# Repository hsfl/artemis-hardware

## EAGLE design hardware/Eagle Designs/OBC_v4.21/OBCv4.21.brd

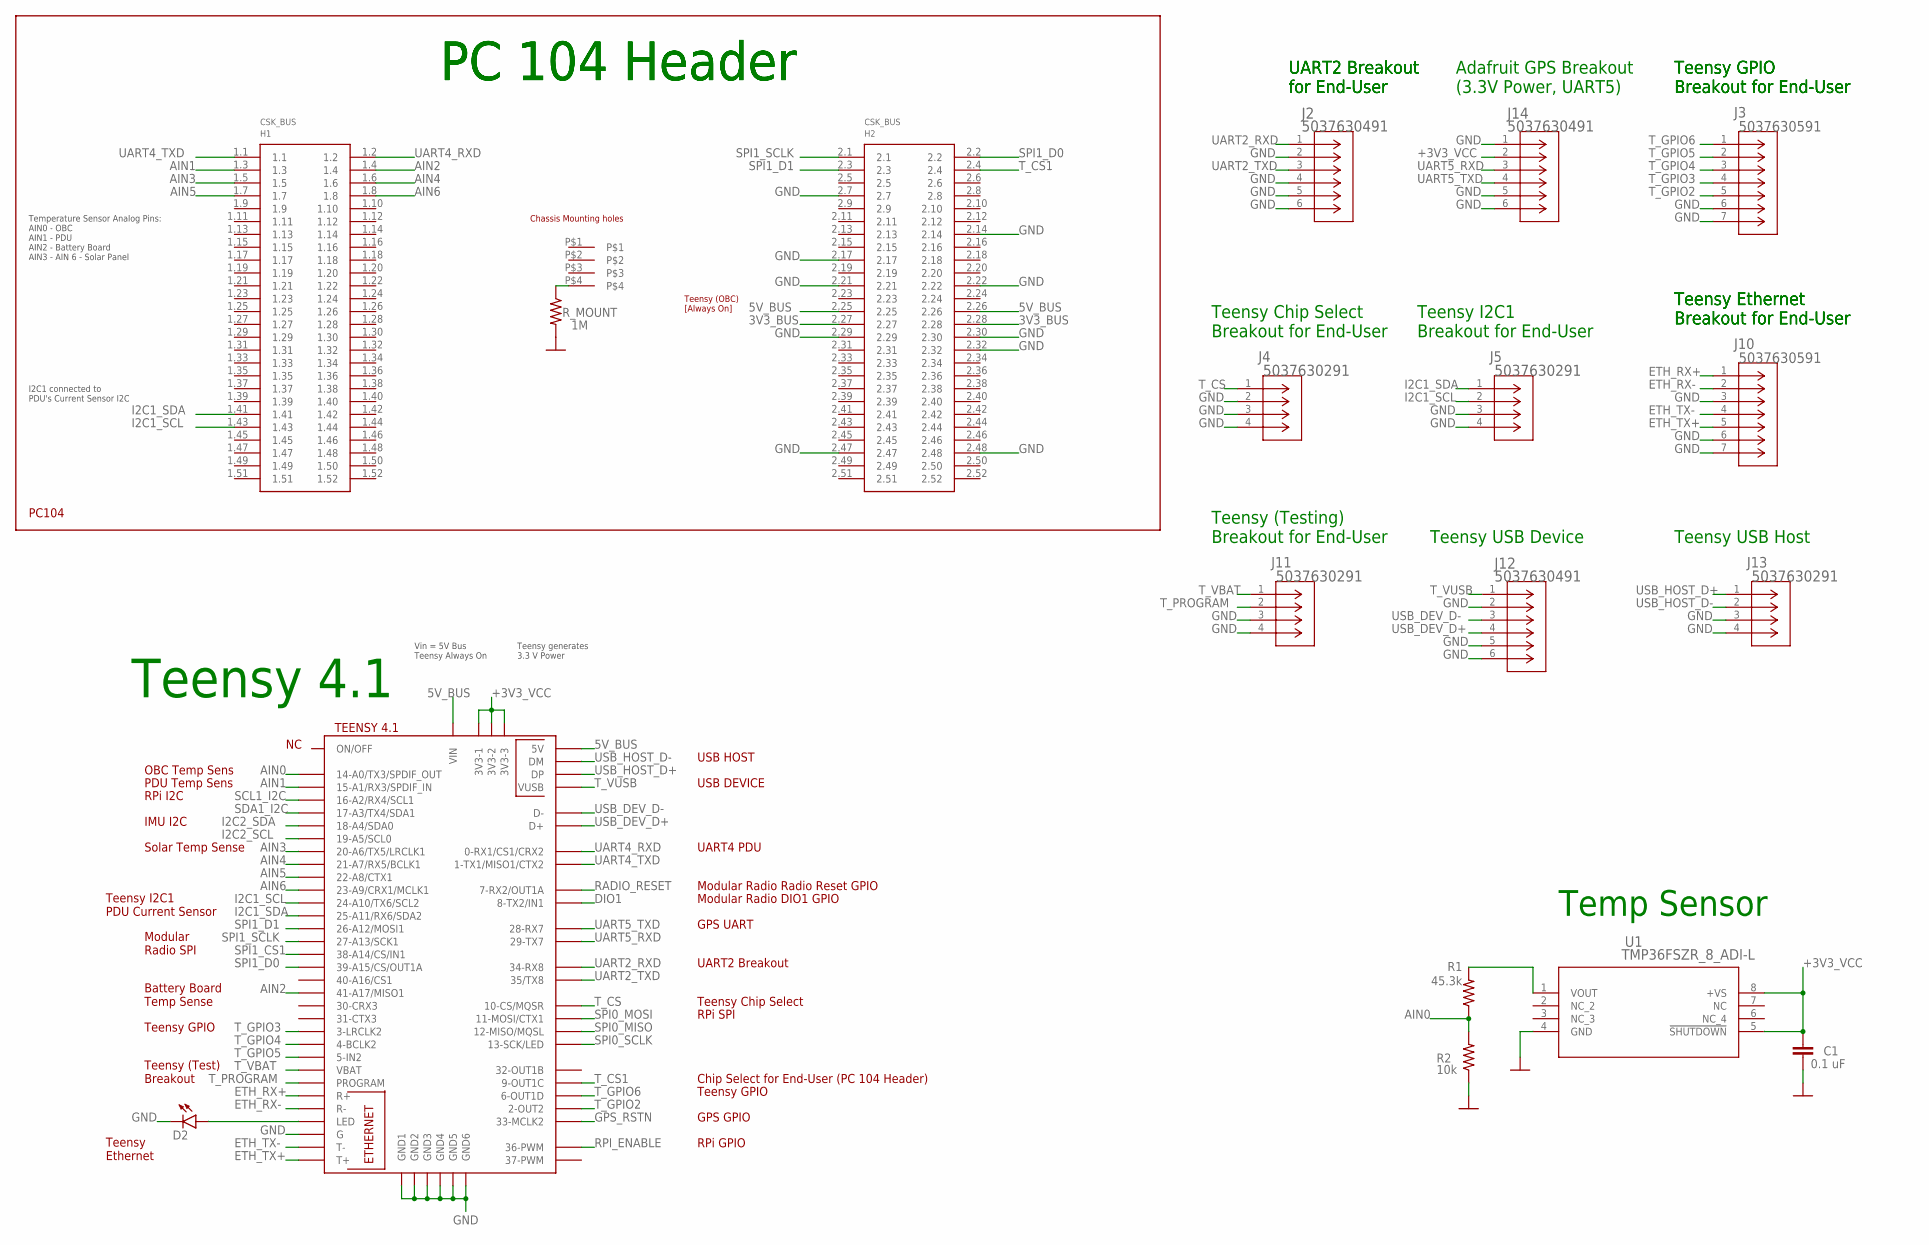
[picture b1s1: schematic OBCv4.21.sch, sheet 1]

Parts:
C1: 0.1 uF; 0805
D2: LEDCHIP-LED0603; CHIP-LED0603
H1: PC104_WCONN
J2, J12, J14: 5037630491; CON_5037630491
J3, J10: 5037630591; CON_5037630591
J4, J5, J11, J13: 5037630291; CON_5037630291
R1: 45.3k; 0805
R2: 10k; 0805
R_MOUNT: 1M; 0805
U1: TMP36FSZR_8_ADI-L; R_8_ADI-L
U$1: TEENSY41

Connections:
3V3_BUS: H1.2.27, H1.2.28; also elsewhere on the board
5V_BUS: H1.2.25, H1.2.26, U$1.+5V (5V), U$1.VIN; also elsewhere on the board
+3V3_VCC: C1.1, J14.2, U1.5 (!SHUTDOWN), U1.8 (+VS), U$1.3V3-1, U$1.3V3-2, U$1.3V3-3; also elsewhere on the board
AIN0: R1.1, R2.2, U$1.14-A0/TX3/SPDIF_OUT
AIN1: H1.1.3, U$1.15-A1/RX3/SPDIF_IN
AIN2: H1.1.4, U$1.41-A17/MISO1
AIN3: H1.1.5, U$1.20-A6/TX5/LRCLK1
AIN4: H1.1.6, U$1.21-A7/RX5/BCLK1
AIN5: H1.1.7, U$1.22-A8/CTX1
AIN6: H1.1.8, U$1.23-A9/CRX1/MCLK1
DIO1: U$1.8-TX2/IN1; also elsewhere on the board
ETH_RX+: J10.1, U$1.R+
ETH_RX-: J10.2, U$1.R-
ETH_TX+: J10.5, U$1.T+
ETH_TX-: J10.4, U$1.T-
GND: C1.2, D2.C, H1.2.7, H1.2.14, H1.2.17, H1.2.21, H1.2.22, H1.2.29, H1.2.30, H1.2.32, H1.2.47, H1.2.48, J2.2, J2.4, J2.5, J2.6, J3.6, J3.7, J4.2, J4.3, J4.4, J5.3, J5.4, J10.3, J10.6, J10.7, J11.3, J11.4, J12.2, J12.5, J12.6, J13.3, J13.4, J14.1, J14.5, J14.6, R2.1, R_MOUNT.2, U1.4 (GND), U$1.G, U$1.GND1, U$1.GND2, U$1.GND3, U$1.GND4, U$1.GND5, U$1.GND6; also elsewhere on the board
GPS_RSTN: U$1.33-MCLK2; also elsewhere on the board
I2C1_SCL: H1.1.43, J5.2, U$1.24-A10/TX6/SCL2
I2C1_SDA: H1.1.41, J5.1, U$1.25-A11/RX6/SDA2
I2C2_SCL: U$1.19-A5/SCL0; also elsewhere on the board
I2C2_SDA: U$1.18-A4/SDA0; also elsewhere on the board
unnamed: D2.A, U$1.LED
unnamed: R1.2, U1.1 (VOUT)
unnamed: H1.P$4, R_MOUNT.1
RADIO_RESET: U$1.7-RX2/OUT1A; also elsewhere on the board
RPI_ENABLE: U$1.36-PWM; also elsewhere on the board
SCL1_I2C: U$1.16-A2/RX4/SCL1; also elsewhere on the board
SDA1_I2C: U$1.17-A3/TX4/SDA1; also elsewhere on the board
SPI0_MISO: U$1.12-MISO/MQSL; also elsewhere on the board
SPI0_MOSI: U$1.11-MOSI/CTX1; also elsewhere on the board
SPI0_SCLK: U$1.13-SCK/LED; also elsewhere on the board
SPI1_CS1: U$1.38-A14/CS/IN1; also elsewhere on the board
SPI1_D0: H1.2.2, U$1.39-A15/CS/OUT1A; also elsewhere on the board
SPI1_D1: H1.2.3, U$1.26-A12/MOSI1; also elsewhere on the board
SPI1_SCLK: H1.2.1, U$1.27-A13/SCK1; also elsewhere on the board
T_CS: J4.1, U$1.10-CS\MQSR (10-CS/MQSR)
T_CS1: H1.2.4, U$1.9-OUT1C
T_GPIO2: J3.5, U$1.2-OUT2
T_GPIO3: J3.4, U$1.3-LRCLK2
T_GPIO4: J3.3, U$1.4-BCLK2
T_GPIO5: J3.2, U$1.5-IN2
T_GPIO6: J3.1, U$1.6-OUT1D
T_PROGRAM: J11.2, U$1.PROGRAM
T_VBAT: J11.1, U$1.VBAT
T_VUSB: J12.1, U$1.VUSB
UART2_RXD: J2.1, U$1.34-RX8
UART2_TXD: J2.3, U$1.35-TX8 (35/TX8)
UART4_RXD: H1.1.2, U$1.0-RX1/CS1/CRX2
UART4_TXD: H1.1.1, U$1.1-TX1/MISO1/CTX2
UART5_RXD: J14.3, U$1.29-TX7; also elsewhere on the board
UART5_TXD: J14.4, U$1.28-RX7; also elsewhere on the board
USB_DEV_D+: J12.4, U$1.D+
USB_DEV_D-: J12.3, U$1.D-
USB_HOST_D+: J13.1, U$1.DP
USB_HOST_D-: J13.2, U$1.DM

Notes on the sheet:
Temp Sensor
PC 104 Header
Temperature Sensor Analog Pins: AIN0 - OBC AIN1 - PDU AIN2 - Battery Board AIN3 - AIN 6 - Solar Panel
UART2 Breakout for End-User
Teensy 4.1
Teensy GPIO Breakout for End-User
Teensy Chip Select Breakout for End-User
Teensy I2C1 Breakout for End-User
OBC Temp Sens
PDU Temp Sens
RPi I2C
IMU I2C
Solar Temp Sense
Teensy I2C1 PDU Current Sensor
Modular Radio SPI
Battery Board Temp Sense
Teensy GPIO
Teensy (Test) Breakout
Teensy Ethernet
RPi GPIO
GPS GPIO
RPi SPI
Teensy Chip Select
UART2 Breakout
GPS UART
Modular Radio Radio Reset GPIO
UART4 PDU
USB HOST
USB DEVICE
Teensy Ethernet Breakout for End-User
Teensy (Testing) Breakout for End-User
Teensy USB Device
Teensy USB Host
Teensy (OBC) [Always On]
Vin = 5V Bus Teensy Always On
Teensy generates 3.3 V Power
Adafruit GPS Breakout (3.3V Power, UART5)
Modular Radio DIO1 GPIO
I2C1 connected to PDU's Current Sensor I2C
Chip Select for End-User (PC 104 Header)

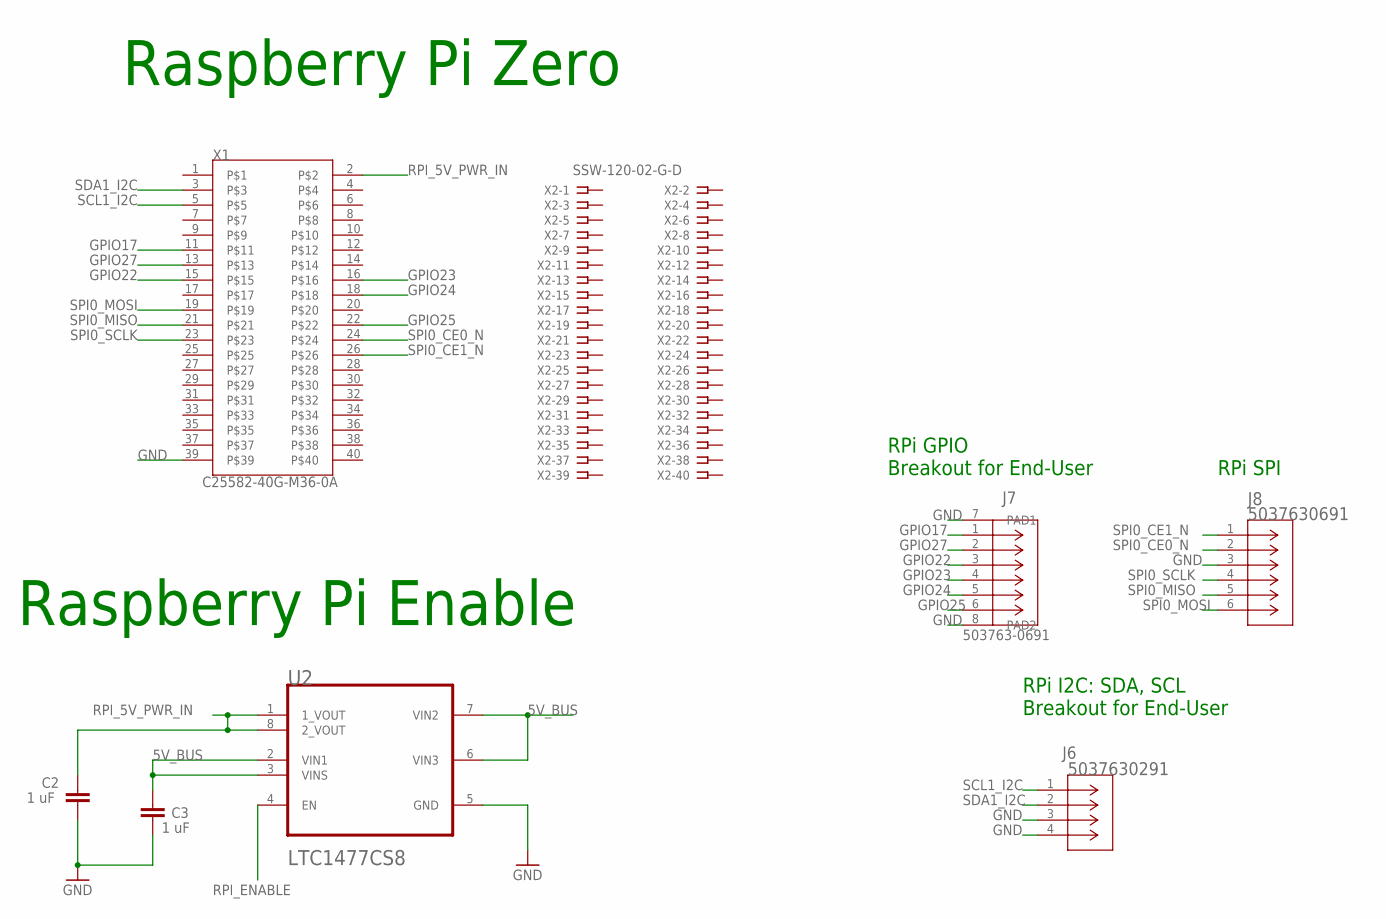
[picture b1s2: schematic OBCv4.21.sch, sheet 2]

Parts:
C2, C3: 1 uF; 0805
J6: 5037630291; CON_5037630291
J7: 503763-0691; CONN_503763-0691_MOL
J8: 5037630691; CONN_503763-0691_MOL
U2: LTC1477CS8LINEAR_TECHNOLOGY_LTC1477CS8_0_2; LINEAR_TECHNOLOGY_LTC1477CS8_2
X1: C25582-40G-M36-0A; ADAFRUIT_C25582-40G-M36-0A_0
X2: SSW-120-02-G-D

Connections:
5V_BUS: C3.1, U2.2 (VIN1), U2.3 (VINS), U2.6 (VIN3), U2.7 (VIN2); also elsewhere on the board
GND: C2.2, C3.2, J6.3, J6.4, J7.7 (PAD1), J7.8 (PAD2), J8.3, U2.5 (GND), X1.39; also elsewhere on the board
GPIO17: J7.1, X1.11
GPIO22: J7.3, X1.15
GPIO23: J7.4, X1.16
GPIO24: J7.5, X1.18
GPIO25: J7.6, X1.22
GPIO27: J7.2, X1.13
RPI_5V_PWR_IN: C2.1, U2.1 (1_VOUT), U2.8 (2_VOUT), X1.2
RPI_ENABLE: U2.4 (EN); also elsewhere on the board
SCL1_I2C: J6.1, X1.5; also elsewhere on the board
SDA1_I2C: J6.2, X1.3; also elsewhere on the board
SPI0_CE0_N: J8.2, X1.24
SPI0_CE1_N: J8.1, X1.26
SPI0_MISO: J8.5, X1.21; also elsewhere on the board
SPI0_MOSI: J8.6, X1.19; also elsewhere on the board
SPI0_SCLK: J8.4, X1.23; also elsewhere on the board

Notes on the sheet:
Raspberry Pi Zero
Raspberry Pi Enable
RPi I2C: SDA, SCL Breakout for End-User
RPi GPIO Breakout for End-User
RPi SPI

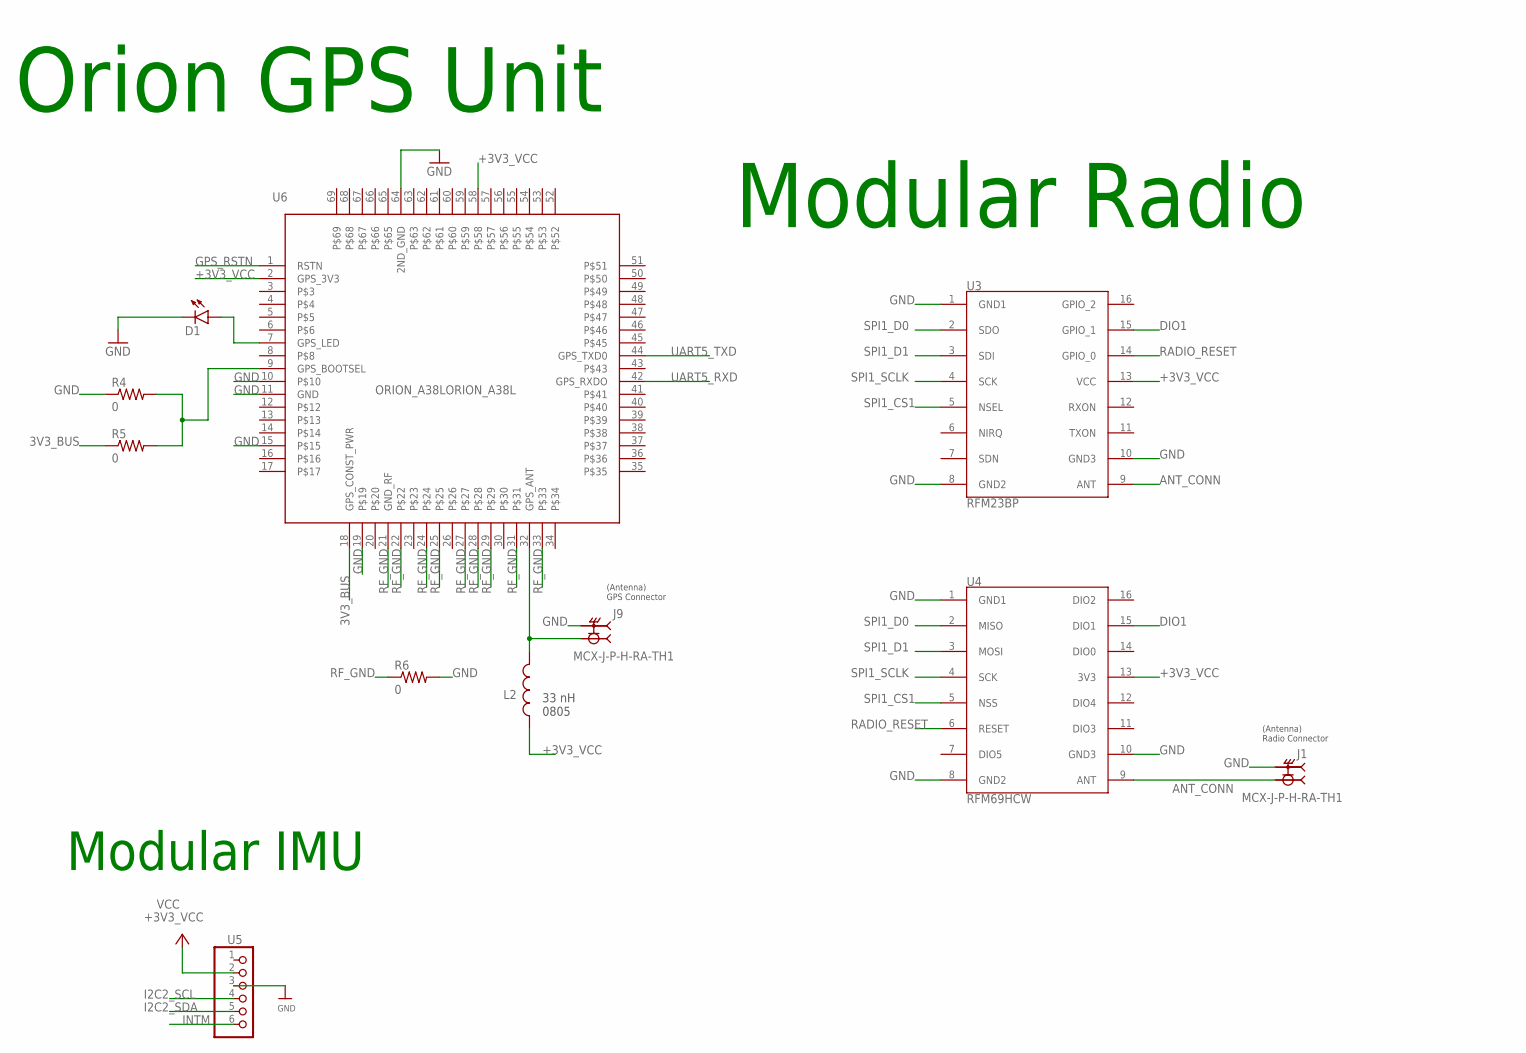
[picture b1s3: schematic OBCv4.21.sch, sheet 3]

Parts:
D1: LEDCHIP-LED0603; CHIP-LED0603
J1, J9: MCX-J-P-H-RA-TH1; SAMTEC_MCX-J-P-H-RA-TH1
L2: AIMC-0805-2N2S-T; INDC2012X105N
R4, R5, R6: 0; 0805
U3: RFM23BP
U4: RFM69HCW
U5: HEADER-1X670MIL; 1X06_ROUND_70
U6: ORION_A38LORION_A38L; ORION_A38L

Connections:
3V3_BUS: R5.1, U6.18 (GPS_CONST_PWR); also elsewhere on the board
+3V3_VCC: L2.1, U3.13 (VCC), U4.13 (3V3), U5.2, U6.2 (GPS_3V3), U6.58; also elsewhere on the board
ANT_CONN: J1.1, U3.9 (ANT), U4.9 (ANT)
DIO1: U3.15 (GPIO_1), U4.15 (DIO1); also elsewhere on the board
GND: D1.C, J1.S1 (2), J1.S2 (2), J1.S3 (2), J1.S4 (2), J9.S1 (2), J9.S2 (2), J9.S3 (2), J9.S4 (2), R4.1, R6.2, U3.1 (GND1), U3.8 (GND2), U3.10 (GND3), U4.1 (GND1), U4.8 (GND2), U4.10 (GND3), U5.3, U6.10, U6.11 (GND), U6.15, U6.19, U6.64 (2ND_GND); also elsewhere on the board
GPS_RSTN: U6.1 (RSTN); also elsewhere on the board
I2C2_SCL: U5.4; also elsewhere on the board
I2C2_SDA: U5.5; also elsewhere on the board
INTM: U5.6
unnamed: R4.2, R5.2, U6.9 (GPS_BOOTSEL)
unnamed: J9.1, L2.2, U6.32 (GPS_ANT)
unnamed: D1.A, U6.7 (GPS_LED)
RADIO_RESET: U3.14 (GPIO_0), U4.6 (RESET); also elsewhere on the board
RF_GND: R6.1, U6.21 (GND_RF), U6.22, U6.24, U6.25, U6.27, U6.28, U6.29, U6.31, U6.33
SPI1_CS1: U3.5 (NSEL), U4.5 (NSS); also elsewhere on the board
SPI1_D0: U3.2 (SDO), U4.2 (MISO); also elsewhere on the board
SPI1_D1: U3.3 (SDI), U4.3 (MOSI); also elsewhere on the board
SPI1_SCLK: U3.4 (SCK), U4.4 (SCK); also elsewhere on the board
UART5_RXD: U6.42 (GPS_RXDO); also elsewhere on the board
UART5_TXD: U6.44 (GPS_TXD0); also elsewhere on the board

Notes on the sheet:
Orion GPS Unit
Modular Radio
Modular IMU
(Antenna) Radio Connector
(Antenna) GPS Connector
33 nH 0805

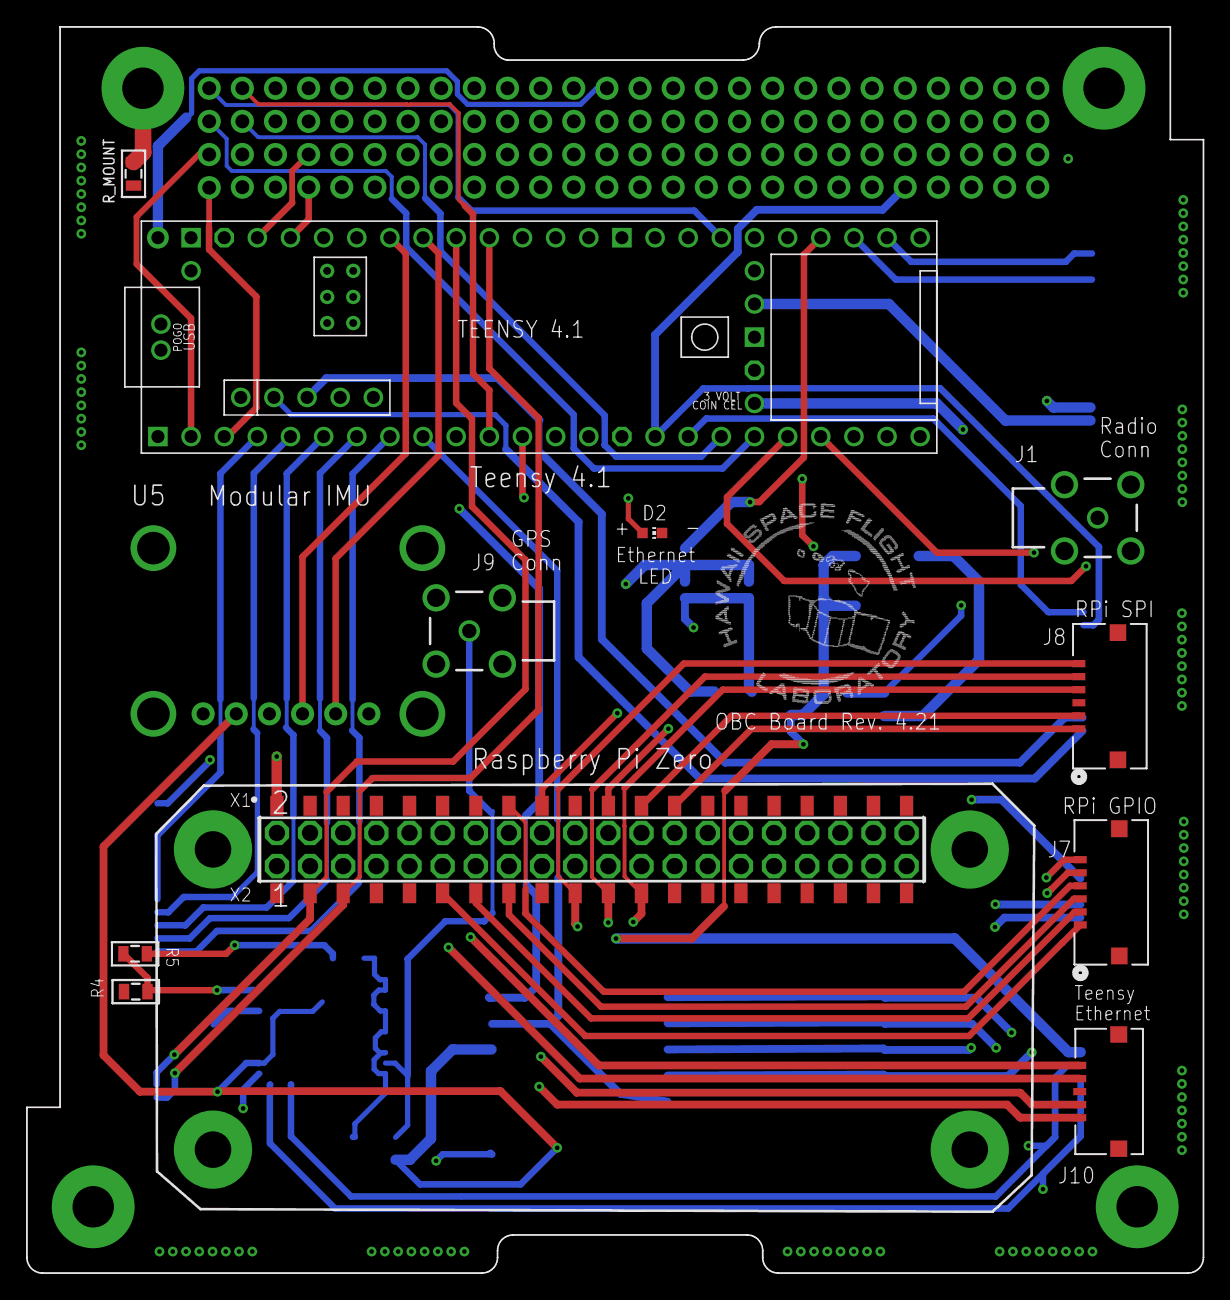
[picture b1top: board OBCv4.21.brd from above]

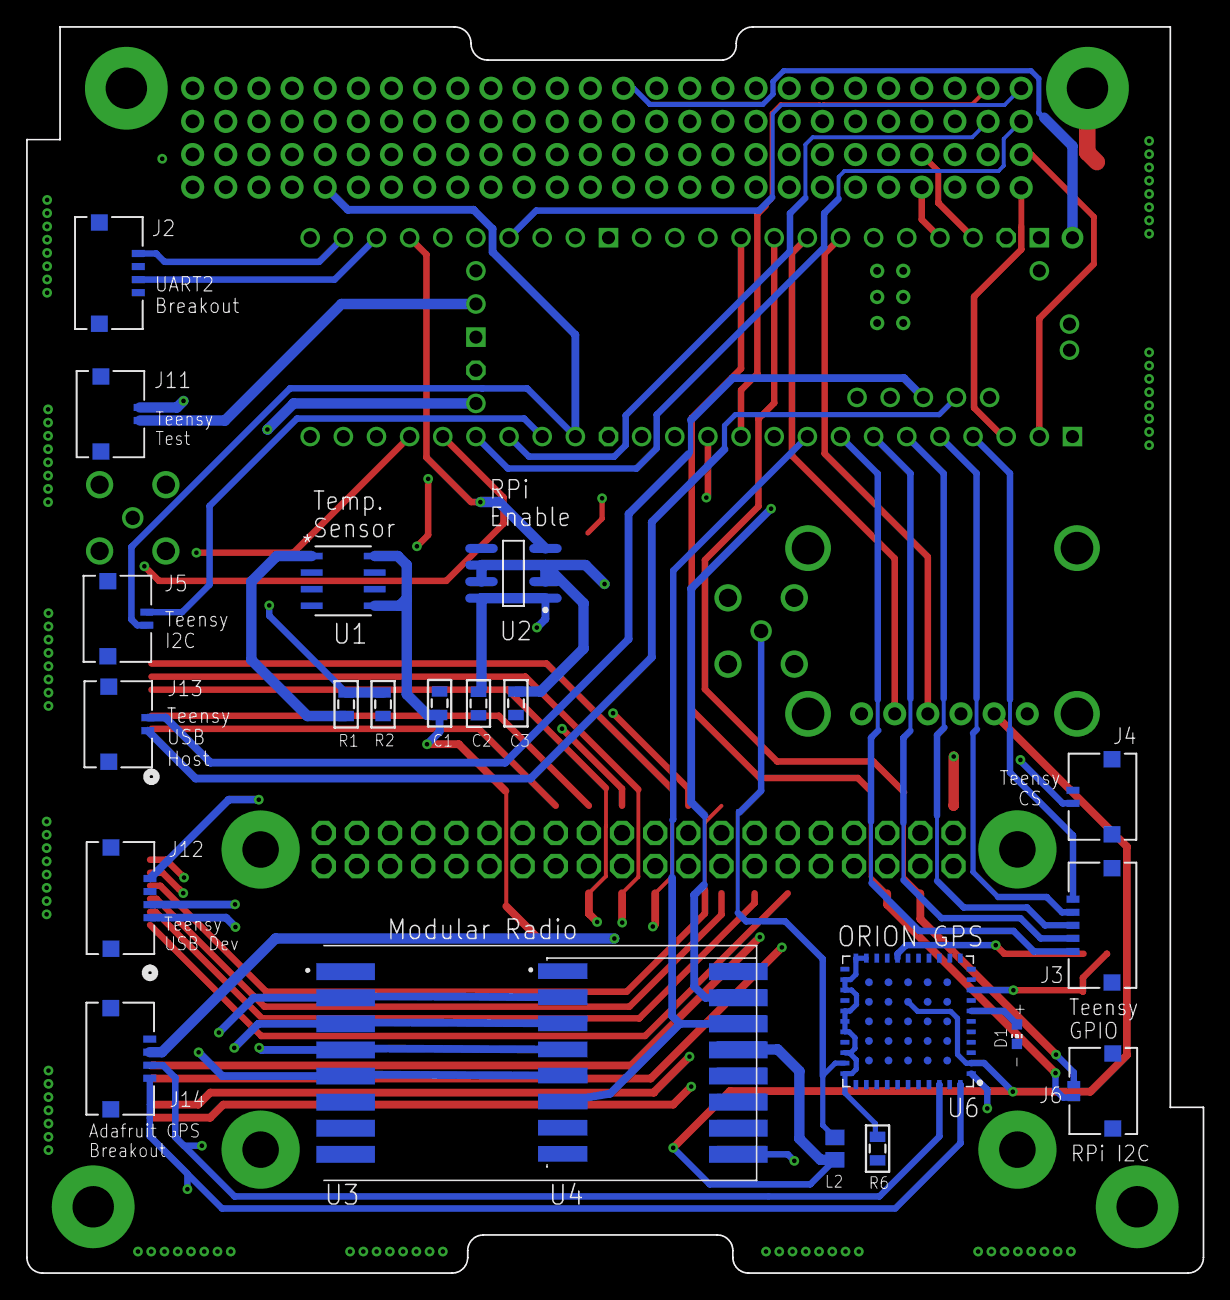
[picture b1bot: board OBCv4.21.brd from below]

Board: 4 copper layers, 90.2 x 95.5 mm, 36 parts (22 on the bottom side), 69 nets.

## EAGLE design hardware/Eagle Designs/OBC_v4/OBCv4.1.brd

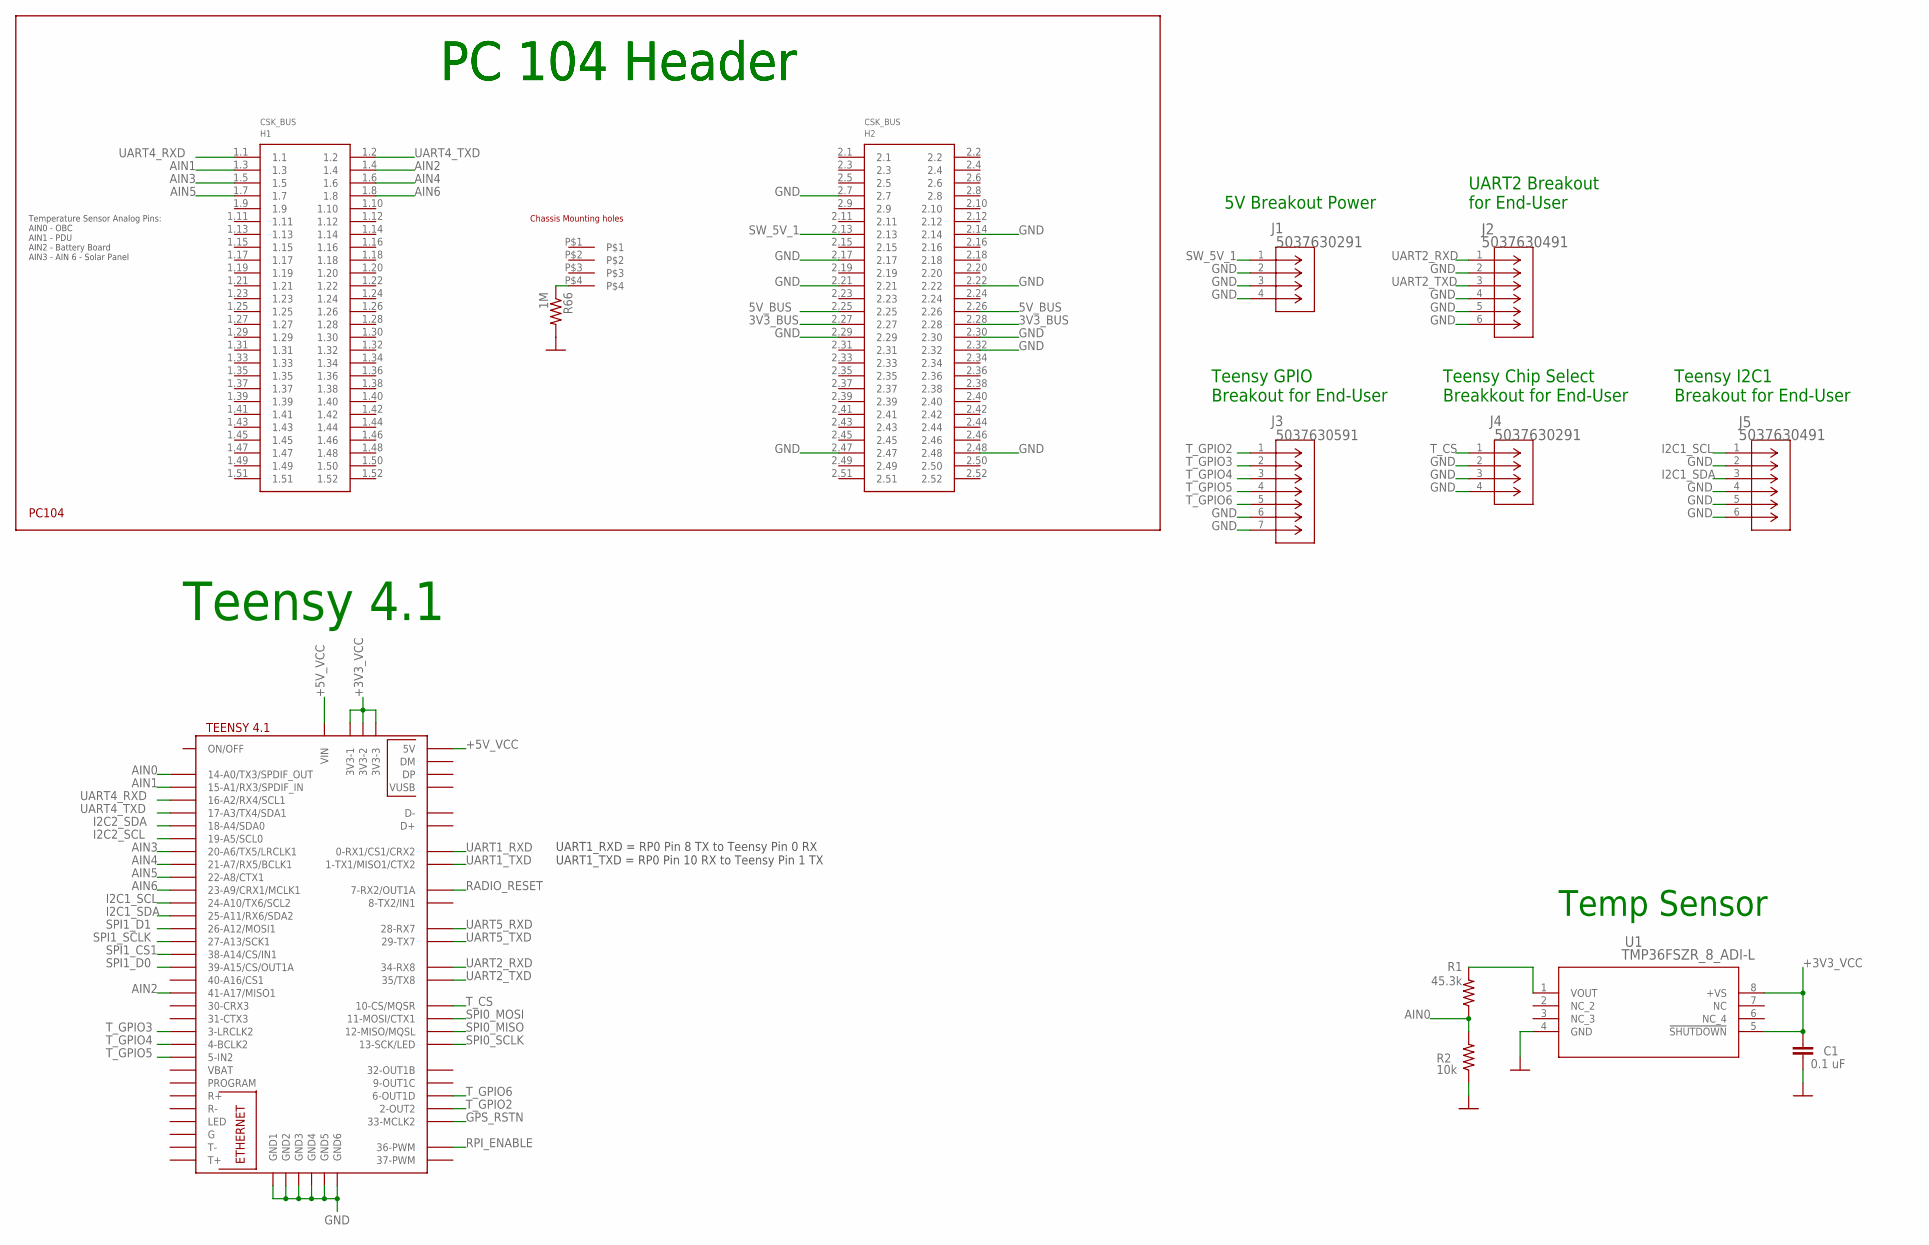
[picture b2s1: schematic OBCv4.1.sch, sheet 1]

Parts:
C1: 0.1 uF; 0805
H1: PC104_WCONN
J1, J4: 5037630291; CON_5037630291
J2, J5: 5037630491; CON_5037630491
J3: 5037630591; CON_5037630591
R1: 45.3k; 0805
R2: 10k; 0805
R66: 1M; 0805
U1: TMP36FSZR_8_ADI-L; R_8_ADI-L
U$1: TEENSY41

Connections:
3V3_BUS: H1.2.27, H1.2.28; also elsewhere on the board
5V_BUS: H1.2.25, H1.2.26
+3V3_VCC: C1.1, U1.5 (!SHUTDOWN), U1.8 (+VS), U$1.3V3-1, U$1.3V3-3; also elsewhere on the board
+5V_VCC: U$1.+5V (5V), U$1.VIN; also elsewhere on the board
AIN0: R1.1, R2.2, U$1.14-A0/TX3/SPDIF_OUT
AIN1: H1.1.3, U$1.15-A1/RX3/SPDIF_IN
AIN2: H1.1.4, U$1.41-A17/MISO1
AIN3: H1.1.5, U$1.20-A6/TX5/LRCLK1
AIN4: H1.1.6, U$1.21-A7/RX5/BCLK1
AIN5: H1.1.7, U$1.22-A8/CTX1
AIN6: H1.1.8, U$1.23-A9/CRX1/MCLK1
GND: C1.2, H1.2.7, H1.2.14, H1.2.17, H1.2.21, H1.2.22, H1.2.29, H1.2.30, H1.2.32, H1.2.47, H1.2.48, J1.2, J1.3, J1.4, J2.2, J2.4, J2.5, J2.6, J3.6, J3.7, J4.2, J4.3, J4.4, J5.2, J5.4, J5.5, J5.6, R2.1, R66.2, U1.4 (GND), U$1.GND1, U$1.GND2, U$1.GND3, U$1.GND4, U$1.GND5, U$1.GND6; also elsewhere on the board
GPS_RSTN: U$1.33-MCLK2; also elsewhere on the board
I2C1_SCL: J5.1, U$1.24-A10/TX6/SCL2
I2C1_SDA: J5.3, U$1.25-A11/RX6/SDA2
I2C2_SCL: U$1.19-A5/SCL0; also elsewhere on the board
I2C2_SDA: U$1.18-A4/SDA0; also elsewhere on the board
unnamed: R1.2, U1.1 (VOUT)
unnamed: H1.P$4, R66.1
RADIO_RESET: U$1.7-RX2/OUT1A; also elsewhere on the board
RPI_ENABLE: U$1.36-PWM; also elsewhere on the board
SPI0_MISO: U$1.12-MISO/MQSL; also elsewhere on the board
SPI0_MOSI: U$1.11-MOSI/CTX1; also elsewhere on the board
SPI0_SCLK: U$1.13-SCK/LED; also elsewhere on the board
SPI1_CS1: U$1.38-A14/CS/IN1; also elsewhere on the board
SPI1_D0: U$1.39-A15/CS/OUT1A; also elsewhere on the board
SPI1_D1: U$1.26-A12/MOSI1; also elsewhere on the board
SPI1_SCLK: U$1.27-A13/SCK1; also elsewhere on the board
SW_5V_1: H1.2.13, J1.1
T_CS: J4.1, U$1.10-CS\MQSR (10-CS/MQSR)
T_GPIO2: J3.1, U$1.2-OUT2
T_GPIO3: J3.2, U$1.3-LRCLK2
T_GPIO4: J3.3, U$1.4-BCLK2
T_GPIO5: J3.4, U$1.5-IN2
T_GPIO6: J3.5, U$1.6-OUT1D
UART1_RXD: U$1.0-RX1/CS1/CRX2; also elsewhere on the board
UART1_TXD: U$1.1-TX1/MISO1/CTX2; also elsewhere on the board
UART2_RXD: J2.1, U$1.34-RX8
UART2_TXD: J2.3, U$1.35-TX8 (35/TX8)
UART4_RXD: H1.1.1, U$1.16-A2/RX4/SCL1
UART4_TXD: H1.1.2, U$1.17-A3/TX4/SDA1
UART5_RXD: U$1.28-RX7; also elsewhere on the board
UART5_TXD: U$1.29-TX7; also elsewhere on the board

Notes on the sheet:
Temp Sensor
PC 104 Header
Temperature Sensor Analog Pins: AIN0 - OBC AIN1 - PDU AIN2 - Battery Board AIN3 - AIN 6 - Solar Panel
5V Breakout Power
UART2 Breakout for End-User
Teensy 4.1
Teensy GPIO Breakout for End-User
Teensy Chip Select Breakkout for End-User
Teensy I2C1 Breakout for End-User
UART1_RXD = RP0 Pin 8 TX to Teensy Pin 0 RX UART1_TXD = RP0 Pin 10 RX to Teensy Pin 1 TX

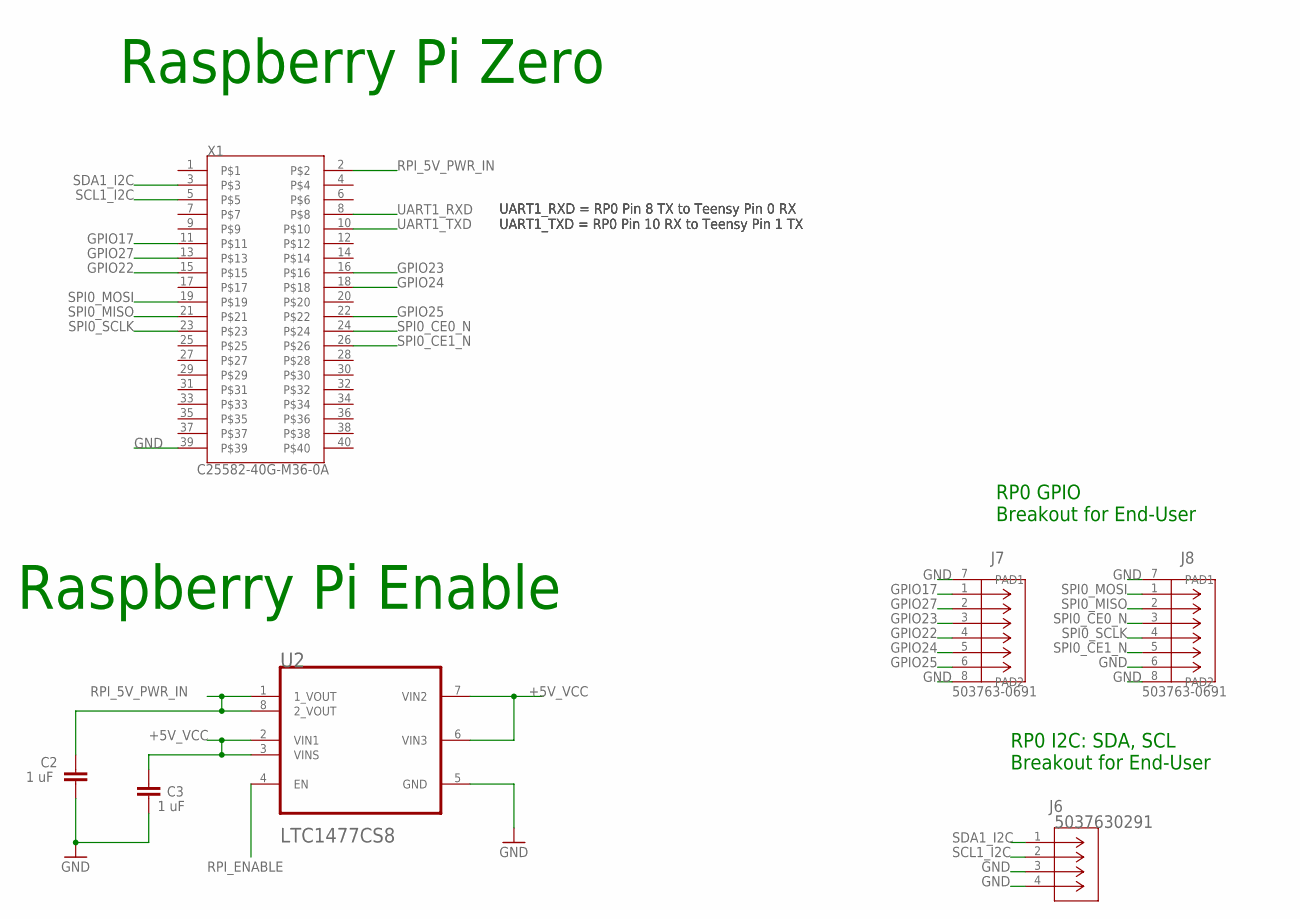
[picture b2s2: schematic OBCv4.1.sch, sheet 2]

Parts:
C2, C3: 1 uF; 0805
J6: 5037630291; CON_5037630291
J7, J8: 503763-0691; CONN_503763-0691_MOL
U2: LTC1477CS8LINEAR_TECHNOLOGY_LTC1477CS8_0_2; LINEAR_TECHNOLOGY_LTC1477CS8_2
X1: C25582-40G-M36-0A; ADAFRUIT_C25582-40G-M36-0A_0

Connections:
+5V_VCC: C3.1, U2.2 (VIN1), U2.3 (VINS), U2.6 (VIN3), U2.7 (VIN2); also elsewhere on the board
GND: C2.2, C3.2, J6.3, J6.4, J7.7 (PAD1), J7.8 (PAD2), J8.6, J8.7 (PAD1), J8.8 (PAD2), U2.5 (GND), X1.39; also elsewhere on the board
GPIO17: J7.1, X1.11
GPIO22: J7.4, X1.15
GPIO23: J7.3, X1.16
GPIO24: J7.5, X1.18
GPIO25: J7.6, X1.22
GPIO27: J7.2, X1.13
RPI_5V_PWR_IN: C2.1, U2.1 (1_VOUT), U2.8 (2_VOUT), X1.2
RPI_ENABLE: U2.4 (EN); also elsewhere on the board
SCL1_I2C: J6.2, X1.5
SDA1_I2C: J6.1, X1.3
SPI0_CE0_N: J8.3, X1.24
SPI0_CE1_N: J8.5, X1.26
SPI0_MISO: J8.2, X1.21; also elsewhere on the board
SPI0_MOSI: J8.1, X1.19; also elsewhere on the board
SPI0_SCLK: J8.4, X1.23; also elsewhere on the board
UART1_RXD: X1.8; also elsewhere on the board
UART1_TXD: X1.10; also elsewhere on the board

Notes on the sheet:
Raspberry Pi Zero
Raspberry Pi Enable
RP0 I2C: SDA, SCL Breakout for End-User
RP0 GPIO Breakout for End-User
UART1_RXD = RP0 Pin 8 TX to Teensy Pin 0 RX UART1_TXD = RP0 Pin 10 RX to Teensy Pin 1 TX

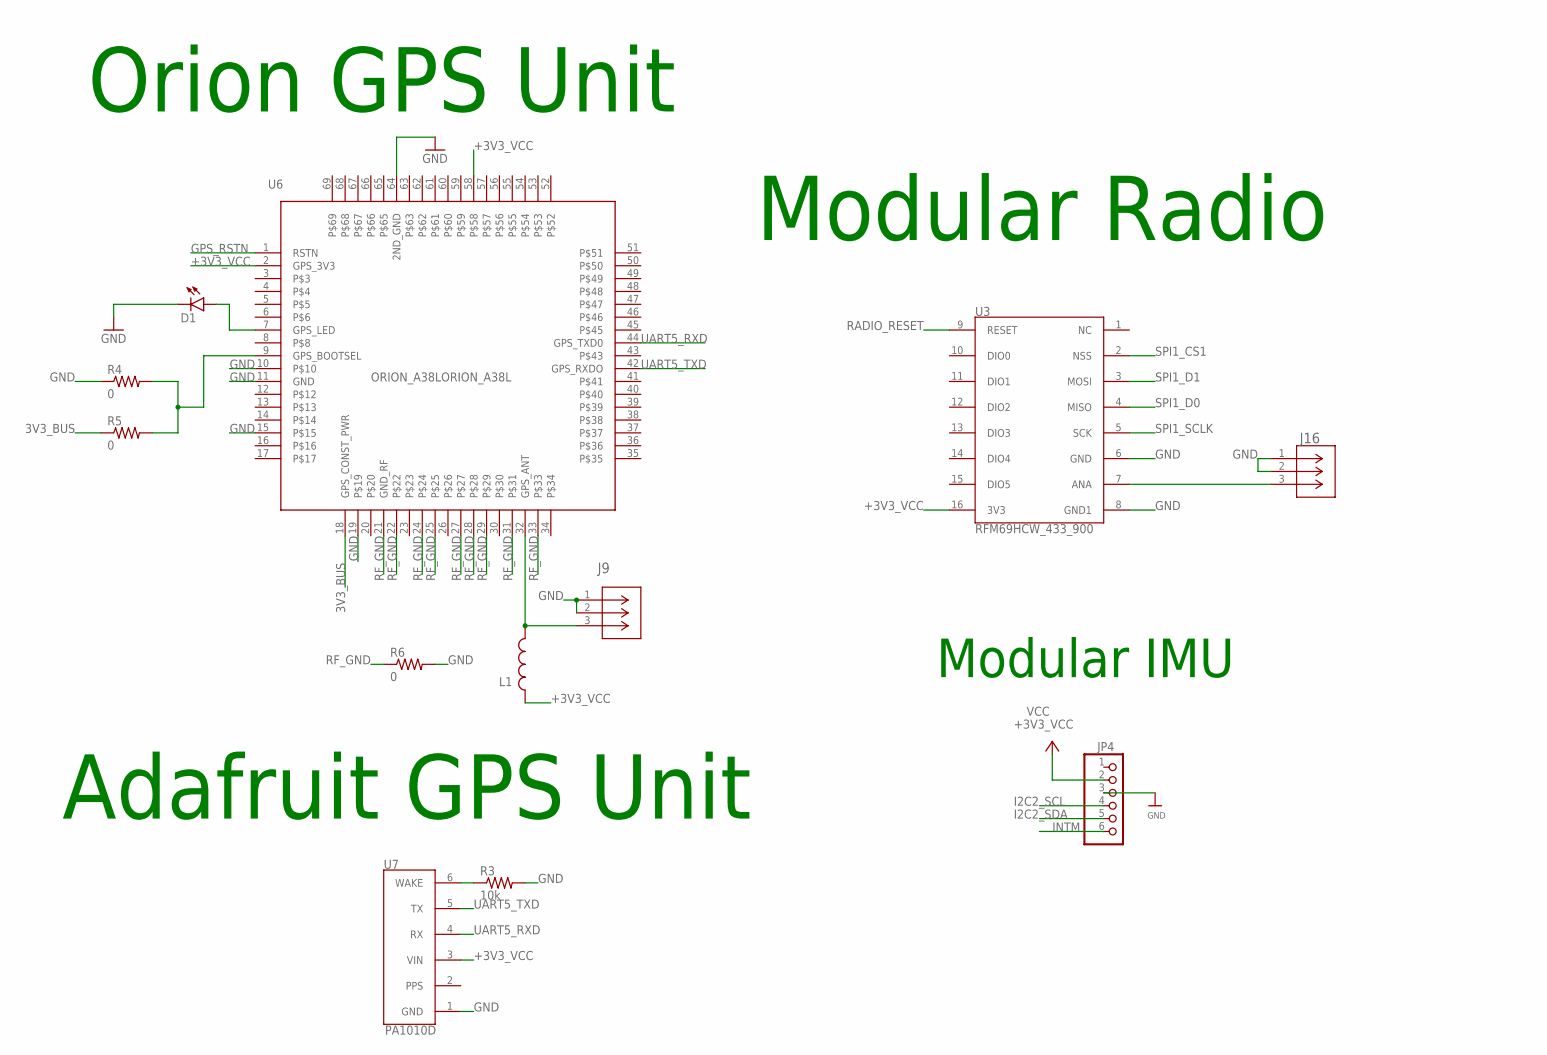
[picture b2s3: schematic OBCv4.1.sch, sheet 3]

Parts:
D1: LEDCHIP-LED0603; CHIP-LED0603
J9, J16: U.FL-R-SMT-1(01); CONN_-SMT-1(01)
JP4: HEADER-1X670MIL; 1X06_ROUND_70
L1: L; INDC2012X145N
R3: 10k; 0805
R4, R5, R6: 0; 0805
U3: RFM69HCW_433_900; RFM69HCW_433
U6: ORION_A38LORION_A38L; ORION_A38L
U7: PA1010D

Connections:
3V3_BUS: R5.1, U6.18 (GPS_CONST_PWR); also elsewhere on the board
+3V3_VCC: JP4.2, L1.1, U3.16 (3V3), U6.2 (GPS_3V3), U6.58, U7.3 (VIN); also elsewhere on the board
GND: D1.C, J9.1, J9.2, J16.1, J16.2, JP4.3, R3.2, R4.1, R6.2, U3.6 (GND), U3.8 (GND1), U6.10, U6.11 (GND), U6.15, U6.19, U6.64 (2ND_GND), U7.1 (GND); also elsewhere on the board
GPS_RSTN: U6.1 (RSTN); also elsewhere on the board
I2C2_SCL: JP4.4; also elsewhere on the board
I2C2_SDA: JP4.5; also elsewhere on the board
INTM: JP4.6
unnamed: J16.3, U3.7 (ANA)
unnamed: R4.2, R5.2, U6.9 (GPS_BOOTSEL)
unnamed: J9.3, L1.2, U6.32 (GPS_ANT)
unnamed: R3.1, U7.6 (WAKE)
unnamed: D1.A, U6.7 (GPS_LED)
RADIO_RESET: U3.9 (RESET); also elsewhere on the board
RF_GND: R6.1, U6.21 (GND_RF), U6.22, U6.24, U6.25, U6.27, U6.28, U6.29, U6.31, U6.33
SPI1_CS1: U3.2 (NSS); also elsewhere on the board
SPI1_D0: U3.4 (MISO); also elsewhere on the board
SPI1_D1: U3.3 (MOSI); also elsewhere on the board
SPI1_SCLK: U3.5 (SCK); also elsewhere on the board
UART5_RXD: U6.44 (GPS_TXD0), U7.4 (RX); also elsewhere on the board
UART5_TXD: U6.42 (GPS_RXDO), U7.5 (TX); also elsewhere on the board

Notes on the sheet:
Orion GPS Unit
Modular Radio
Modular IMU
Adafruit GPS Unit

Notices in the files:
parts and their libraries:
SparkFun-PowerSymbols: Licensing: Creative Commons ShareAlike 4.0 International - https://creativecommons.org/licenses/by-sa/4.0
Improved Molex 503763-0691: COPYRIGHT: Copyright (C) 2018 Accelerated Designs. All rights reserved
COPYRIGHT: Copyright (C) 2021 Ultra Librarian. All rights reserved.
